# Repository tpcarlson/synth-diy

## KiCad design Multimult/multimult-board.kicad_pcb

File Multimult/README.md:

---
typora-root-url: images
---

# Multimult

##### What is this?

An 8hp, 6 way buffered multiple. For each row, the input is *copied* and the copies are sent to the three output jacks. A small indicator LED per row shows the presence of signal. This buffered multiple is *DC coupled*, which means it's great for both audio and CV use.

##### How much power does it use?

As measured by the joranalogue Test 3, around 50mA on +12v and similar on -12v at peak. The 5v rail is unused.

##### Where does the design come from?

The schematic is based on the Music from outer space DC coupled Voltage Distributor #2, with some tweaks. You can find the original schematics on the MFOS site (http://musicfromouterspace.com/index.php?MAINTAB=SYNTHDIY&VPW=1252&VPH=500).

##### Are there any rare/weird parts used?

No. The design specifies a two-colour LED per input, so you could substitute that for a single colour LED if you only care about positive voltages.

##### Are there any problems with the design?

Not that I'm aware of. Other buffered multiple schematics seem to add a high resistance path to ground for the opamp inputs, but the MFOS design did not - so I skipped it as well. It's worth soldering the two-colour LEDs last after verifying that the positive and negative colours are the right way around - the first LED I soldered red was positive and green negative! A really easy way to check this is to power up the module, feed it some known signals and just touch the legs of your LED to the pads for the LEDs.

##### Do you have a BOM/Mouser cart/Tayda links?

Sorry, no. Things go out of stock so frequently it'd be a lot of work to keep these up to date. Everything in this project is easy to source though, so you should not have any trouble.

##### Can I buy PCBs or a kit?

Send me an email (twigathy+synth@gmail.com)...

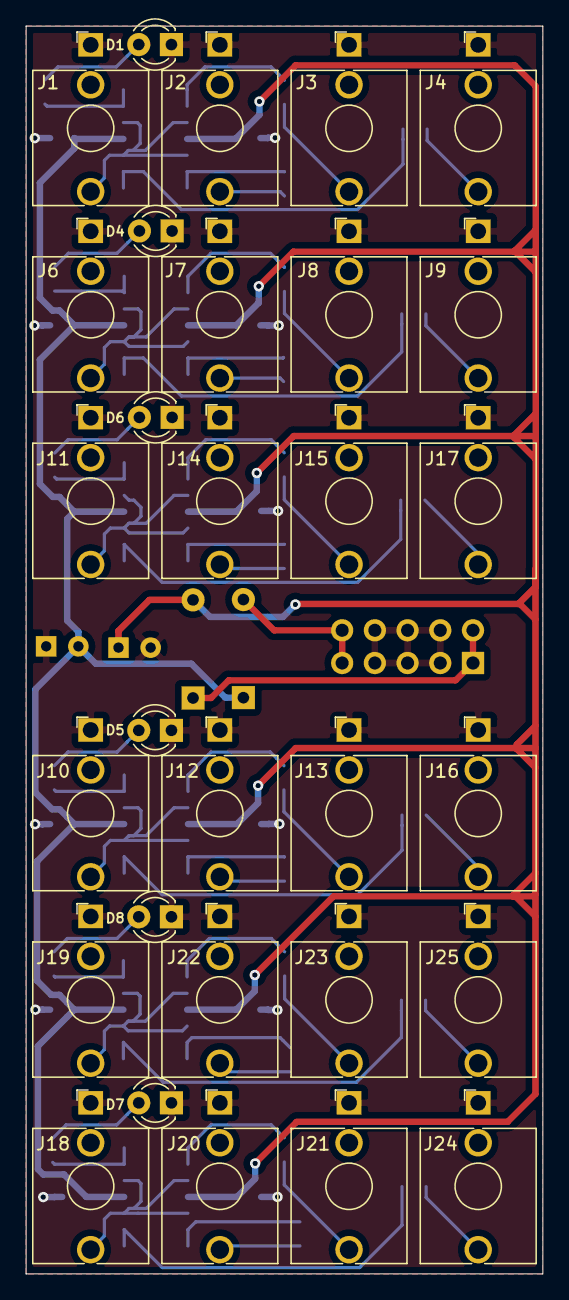
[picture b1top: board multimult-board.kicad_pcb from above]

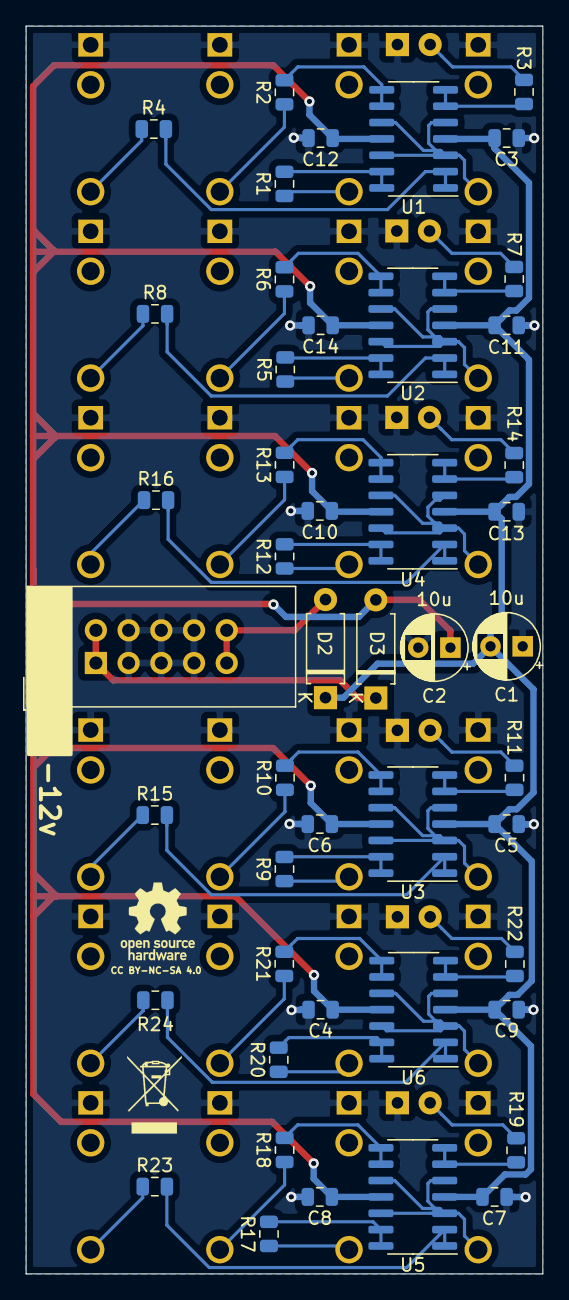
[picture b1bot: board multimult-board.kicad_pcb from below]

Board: 2 copper layers, 40.1 x 96.9 mm, 79 parts (49 on the bottom side), 59 nets.

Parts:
C1, C2: 10u; CP_Radial_D5.0mm_P2.50mm
C3, C4, C5, C6, C7, C8, C9, C10, C11, C12, C13, C14: 100n; C_0805_2012Metric
D1, D4, D5, D6, D7, D8: LED_Dual_2pin; LED_D3.0mm
D2, D3: D_Schottky; D_A-405_P7.62mm_Horizontal
J1, J2, J3, J4, J6, J7, J8, J9, J10, J11, J12, J13, J14, J15, J16, J17, J18, J19, J20, J21, J22, J23, J24, J25: AudioJack2; Jack_3.5mm_QingPu_WQP-PJ398SM_Vertical_CircularHoles
J5: Conn_02x05_Odd_Even; IDC-Header_2x05_P2.54mm_Vertical
J28: WEEE; WEEE-Logo_4.2x6mm_SilkScreen
J29: OSHW; OSHW-Logo_5.7x6mm_SilkScreen
R1, R2, R4, R5, R6, R8, R9, R10, R12, R13, R15, R16, R17, R18, R20, R21, R23, R24: 100R; R_0805_2012Metric
R3, R7, R11, R14, R19, R22: 1k; R_0805_2012Metric
U1, U2, U3, U4, U5, U6: TL074; SOIC-14_3.9x8.7mm_P1.27mm

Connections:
+12V: C1.2, C3.1, C5.1, C7.1, C9.1, C11.1, C13.1, D2.1, U1.4, U2.4, U3.4, U4.4, U5.4, U6.4
-12V: C2.1, C4.1, C6.1, C8.1, C10.1, C12.1, C14.1, D3.2, U1.11, U2.11, U3.11, U4.11, U5.11, U6.11
Earth: C1.1, C2.2, C3.2, C4.2, C5.2, C6.2, C7.2, C8.2, C9.2, C10.2, C11.2, C12.2, C13.2, C14.2, D1.1, D4.1, D5.1, D6.1, D7.1, D8.1, J1.S, J2.S, J3.S, J4.S, J5.3, J5.4, J5.5, J5.6, J5.7, J5.8, J6.S, J7.S, J8.S, J9.S, J10.S, J11.S, J12.S, J13.S, J14.S, J15.S, J16.S, J17.S, J18.S, J19.S, J20.S, J21.S, J22.S, J23.S, J24.S, J25.S
unnamed: D1.2, R3.1
unnamed: D2.2, J5.9, J5.10
unnamed: D3.1, J5.1, J5.2
unnamed: D4.2, R7.1
unnamed: D5.2, R11.1
unnamed: D6.2, R14.1
unnamed: D7.2, R19.1
unnamed: D8.2, R22.1
unnamed: J1.T, U1.3, U1.5, U1.10, U1.12
unnamed: J2.T, R1.1
unnamed: J3.T, R2.1
unnamed: J4.T, R4.1
unnamed: J6.T, U2.3, U2.5, U2.10, U2.12
unnamed: J7.T, R5.1
unnamed: J8.T, R6.1
unnamed: J9.T, R8.1
unnamed: J10.T, U3.3, U3.5, U3.10, U3.12
unnamed: J11.T, U4.3, U4.5, U4.10, U4.12
unnamed: J12.T, R9.1
unnamed: J13.T, R10.1
unnamed: J14.T, R12.1
unnamed: J15.T, R13.1
unnamed: J16.T, R15.1
unnamed: J17.T, R16.1
unnamed: J18.T, U5.3, U5.5, U5.10, U5.12
unnamed: J19.T, U6.3, U6.5, U6.10, U6.12
unnamed: J20.T, R17.1
unnamed: J21.T, R18.1
unnamed: J22.T, R20.1
unnamed: J23.T, R21.1
unnamed: J24.T, R23.1
unnamed: J25.T, R24.1
unnamed: R1.2, U1.13, U1.14
unnamed: R2.2, U1.8, U1.9
unnamed: R3.2, U1.6, U1.7
unnamed: R4.2, U1.1, U1.2
unnamed: R5.2, U2.13, U2.14
unnamed: R6.2, U2.8, U2.9
unnamed: R7.2, U2.6, U2.7
unnamed: R8.2, U2.1, U2.2
unnamed: R9.2, U3.13, U3.14
unnamed: R10.2, U3.8, U3.9
unnamed: R11.2, U3.6, U3.7
unnamed: R12.2, U4.13, U4.14
unnamed: R13.2, U4.8, U4.9
unnamed: R14.2, U4.6, U4.7
unnamed: R15.2, U3.1, U3.2
unnamed: R16.2, U4.1, U4.2
unnamed: R17.2, U5.13, U5.14
unnamed: R18.2, U5.8, U5.9
unnamed: R19.2, U5.6, U5.7
unnamed: R20.2, U6.13, U6.14
unnamed: R21.2, U6.8, U6.9
unnamed: R22.2, U6.6, U6.7
unnamed: R23.2, U5.1, U5.2
unnamed: R24.2, U6.1, U6.2

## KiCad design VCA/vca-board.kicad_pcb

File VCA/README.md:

# VCA

##### What is this?

A straightforward 2-channel VCA with CV inputs and an offset per channel. Basically, makes noise quieter (or anything else you want to modulate).

##### How much power does it use?

Next to nothing! Around 10ma on both +/- 12v when both channels are fully "open".

##### Where does the design come from?

This is almost a complete copy of the schematic from [this wonderful ElectricDruid article.](https://electricdruid.net/design-a-eurorack-vintage-vca-with-the-lm13700/)

##### Are there any rare/weird parts used?

The LM13700 is about the most exotic thing in the design, and that can be found pretty much everywhere - I got mine from RS in the UK.

##### Are there any problems with the design?

While the component layout is pretty neat and tidy, the routing is an absolute disaster. In spite of that it all still works and doesn't sound noisy or anything like that.

The resistor footprints on the PCB are also a little small, so I had to stand my resistors up. If you used 1/8th watt resistors they'd probably fit fine.

Finally, I also somehow neglected to add power decoupling for the +/-12v rails at the power connector, but there is reverse polarity protection present.

If I were to give this a second try, I'd add state LEDs to everything (CV, input, output) and probably make the panel just a touch wider to allow for better ergonomics. You might get by with skinny trimmer potentiometers but I'm personally not much of a fan of those.

##### Do you have a BOM/Mouser cart/Tayda links?

Sorry, no. Things go out of stock so frequently it'd be a lot of work to keep these up to date. Everything in this project is easy to source though, so you should not have any trouble.

##### Can I buy PCBs or a kit?

Send me an email (twigathy+synth@gmail.com)...

(Add some rendered images of the panel and back of PCB(s).)

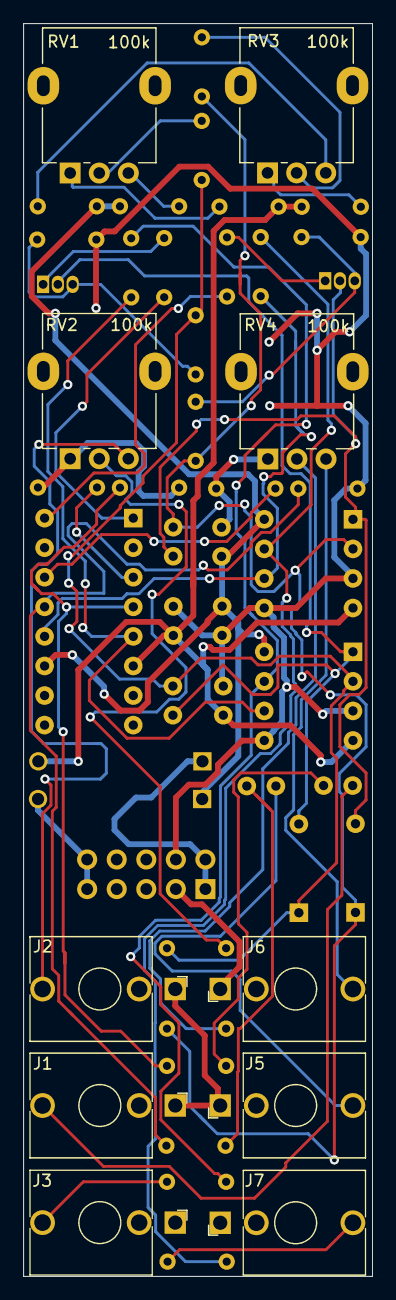
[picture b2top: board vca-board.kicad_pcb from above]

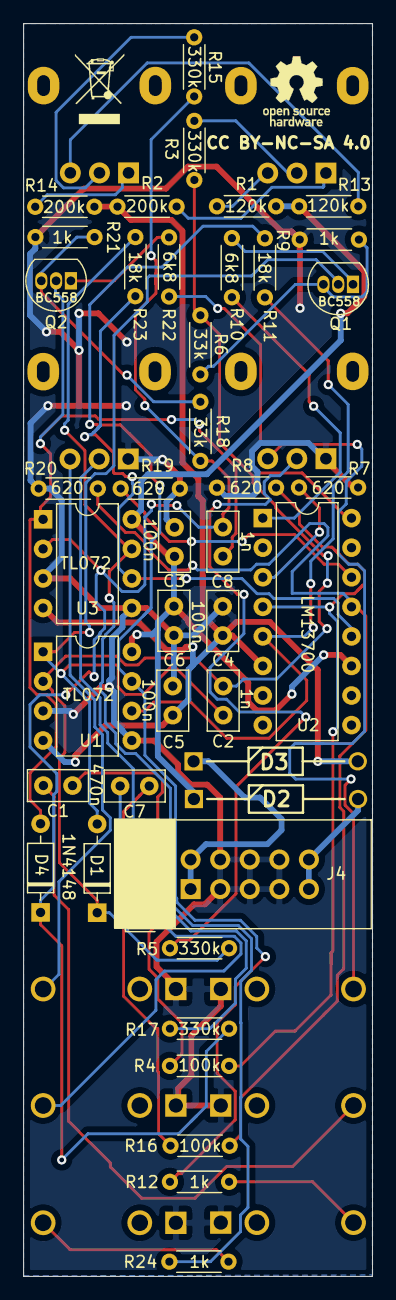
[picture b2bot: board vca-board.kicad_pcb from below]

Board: 2 copper layers, 30.0 x 107.6 mm, 54 parts (44 on the bottom side), 39 nets.

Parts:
C1, C7: 470n; C_Disc_D5.0mm_W2.5mm_P2.50mm
C2, C8: 1n; C_Disc_D5.0mm_W2.5mm_P2.50mm
C3, C4, C5, C6: 100n; C_Disc_D5.0mm_W2.5mm_P2.50mm
D1, D4: 1N4148; D_DO-35_SOD27_P7.62mm_Horizontal
D2, D3: D_Schottky; DIOAD1405W86L465D235
J1, J2, J3, J5, J6, J7: AudioJack2; Jack_3.5mm_QingPu_WQP-PJ398SM_Vertical_CircularHoles
J4: Conn_02x05_Odd_Even; IDC-Header_2x05_P2.54mm_Vertical
J26: WEEE; WEEE-Logo_4.2x6mm_SilkScreen
J27: OSHW; OSHW-Logo_5.7x6mm_SilkScreen
Q1, Q2: BC558; TO-92_Inline
R1, R13: 120k; R_Axial_DIN0204_L3.6mm_D1.6mm_P5.08mm_Horizontal
R2, R14: 200k; R_Axial_DIN0204_L3.6mm_D1.6mm_P5.08mm_Horizontal
R3, R5, R15, R17: 330k; R_Axial_DIN0204_L3.6mm_D1.6mm_P5.08mm_Horizontal
R4, R16: 100k; R_Axial_DIN0204_L3.6mm_D1.6mm_P5.08mm_Horizontal
R6, R18: 33k; R_Axial_DIN0204_L3.6mm_D1.6mm_P5.08mm_Horizontal
R7, R8, R19, R20: 620; R_Axial_DIN0204_L3.6mm_D1.6mm_P5.08mm_Horizontal
R9, R12, R21, R24: 1k; R_Axial_DIN0204_L3.6mm_D1.6mm_P5.08mm_Horizontal
R10, R22: 6k8; R_Axial_DIN0204_L3.6mm_D1.6mm_P5.08mm_Horizontal
R11, R23: 18k; R_Axial_DIN0204_L3.6mm_D1.6mm_P5.08mm_Horizontal
RV1, RV2, RV3, RV4: 100k; Potentiometer_Alpha_RD901F-40-00D_Single_Vertical
U1, U3: TL072; DIP-8_W7.62mm
U2: LM13700; DIP-16_W7.62mm

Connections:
+12V: C3.1, C6.2, D2.1, R1.2, R13.2, U1.8, U2.11, U3.8
-12V: C4.1, C5.1, D3.2, R2.2, R14.2, U1.4, U2.6, U3.4
Earth: C3.2, C4.2, C5.2, C6.1, J1.S, J2.S, J3.S, J4.3, J4.4, J4.5, J4.6, J4.7, J4.8, J5.S, J6.S, J7.S, R7.2, R8.2, R9.1, R19.2, R20.2, R21.1, RV2.1, RV4.1, U1.3, U1.5, U3.3, U3.5
unnamed: C1.1, R4.2
unnamed: C1.2, J1.T
unnamed: C2.1, D1.2, Q1.2, U1.1
unnamed: C2.2, D1.1, R3.1, R5.1, R6.2, U1.2
unnamed: C7.1, R16.2
unnamed: C7.2, J5.T
unnamed: C8.1, D4.2, Q2.2, U3.1
unnamed: C8.2, D4.1, R15.1, R17.1, R18.2, U3.2
unnamed: D2.2, J4.9, J4.10
unnamed: D3.1, J4.1, J4.2
unnamed: J2.T, RV2.3
unnamed: J3.T, R12.1
unnamed: J6.T, RV4.3
unnamed: J7.T, R24.1
unnamed: Q1.1, R10.1
unnamed: Q1.3, R6.1, R9.2
unnamed: Q2.1, R22.1
unnamed: Q2.3, R18.1, R21.2
unnamed: R1.1, RV1.3
unnamed: R2.1, RV1.1
unnamed: R3.2, RV1.2
unnamed: R4.1, R8.1, U2.4
unnamed: R5.2, RV2.2
unnamed: R7.1, U2.3
unnamed: R10.2, U2.1
unnamed: R11.1, R12.2, U1.7
unnamed: R11.2, U1.6, U2.5
unnamed: R13.1, RV3.3
unnamed: R14.1, RV3.1
unnamed: R15.2, RV3.2
unnamed: R16.1, R20.1, U2.13
unnamed: R17.2, RV4.2
unnamed: R19.1, U2.14
unnamed: R22.2, U2.16
unnamed: R23.1, R24.2, U3.7
unnamed: R23.2, U2.12, U3.6

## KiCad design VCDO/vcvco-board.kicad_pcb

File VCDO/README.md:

# VCDO

##### What is this?

A 10hp Wavetable oscillator with 1v/octave control, pitch, bitcrush, glide, and a separate sub-oscillator output.

##### How much power does it use?

As measured by the Joranalogue Test 3, around 40 mA on +12v and 10 mA on -12v at peak. The 5v rail is unused.

##### Where does the design come from?

The original schematic is from the datasheet for the VCDO chip on the ElectricDruid website (https://electricdruid.net/product/vcdo-wavetable-oscillator/). There were a couple of tweaks to add test points and buffered LED drivers for the main and sub-oscillator outputs.

##### Are there any rare/weird parts used?

If you're handy at flashing PIC chips you can flash  your own, however I'd strongly suggest supporting ElectricDruid and buying chips from them directly instead! Other than that, there are no exotic parts used. Some of the resistor values are _little_ less common, but resistors are very cheap. I just got 50-packs of values I didn't have for less than £1 each.

##### Are there any problems with the design?

Quite a few, but nothing that has proven to be a killer so far... Here are some things I'd like to improve if ever there were a v2

- Some of the controls are "reversed", such as the bitcrush, frequency and fine controls. I think this comes from me misreading the original schematic a little. I have not fixed the Kicad schematics here yet!
- The space between the Glide control and Glide toggle is a bit limited. It would have probably been better to mount the Glide toggle just a little further down, between the control and the input jacks
- While I specified a dual-colour LED it turns out that's not really very interesting at VCO rates. You could easily swap that out for a single-colour LED provided you get the polarity right
- The LEDs at the top are a little close to the controls, I made sure only a little of the dome of my LEDs was poking out. If you are building one yourself, you can do this, use a flat-topped LED, or even use light pipes and an SMD LED on the LED pads...
- It would've been nice to include LED indicators for CV parameters, but there was not enough board space, and I'm not really sure where on the panel they could usefully go either
- The vertically mounted resistors work fine, but now that I know SMD assembly isn't really that expensive, maybe go for surface mount and have them pre-soldered next time around
- Calibration trimmers worked fine, but the test points a little fiddly to access - keep them further away from other parts in future

##### Do you have a BOM/Mouser cart/Tayda links?

Sorry, no. Things go out of stock so frequently it'd be a lot of work to keep these up to date. Everything in this project is easy to source though, so you should not have any trouble.

##### Can I buy PCBs or a kit?

Send me an email (twigathy+synth@gmail.com)...

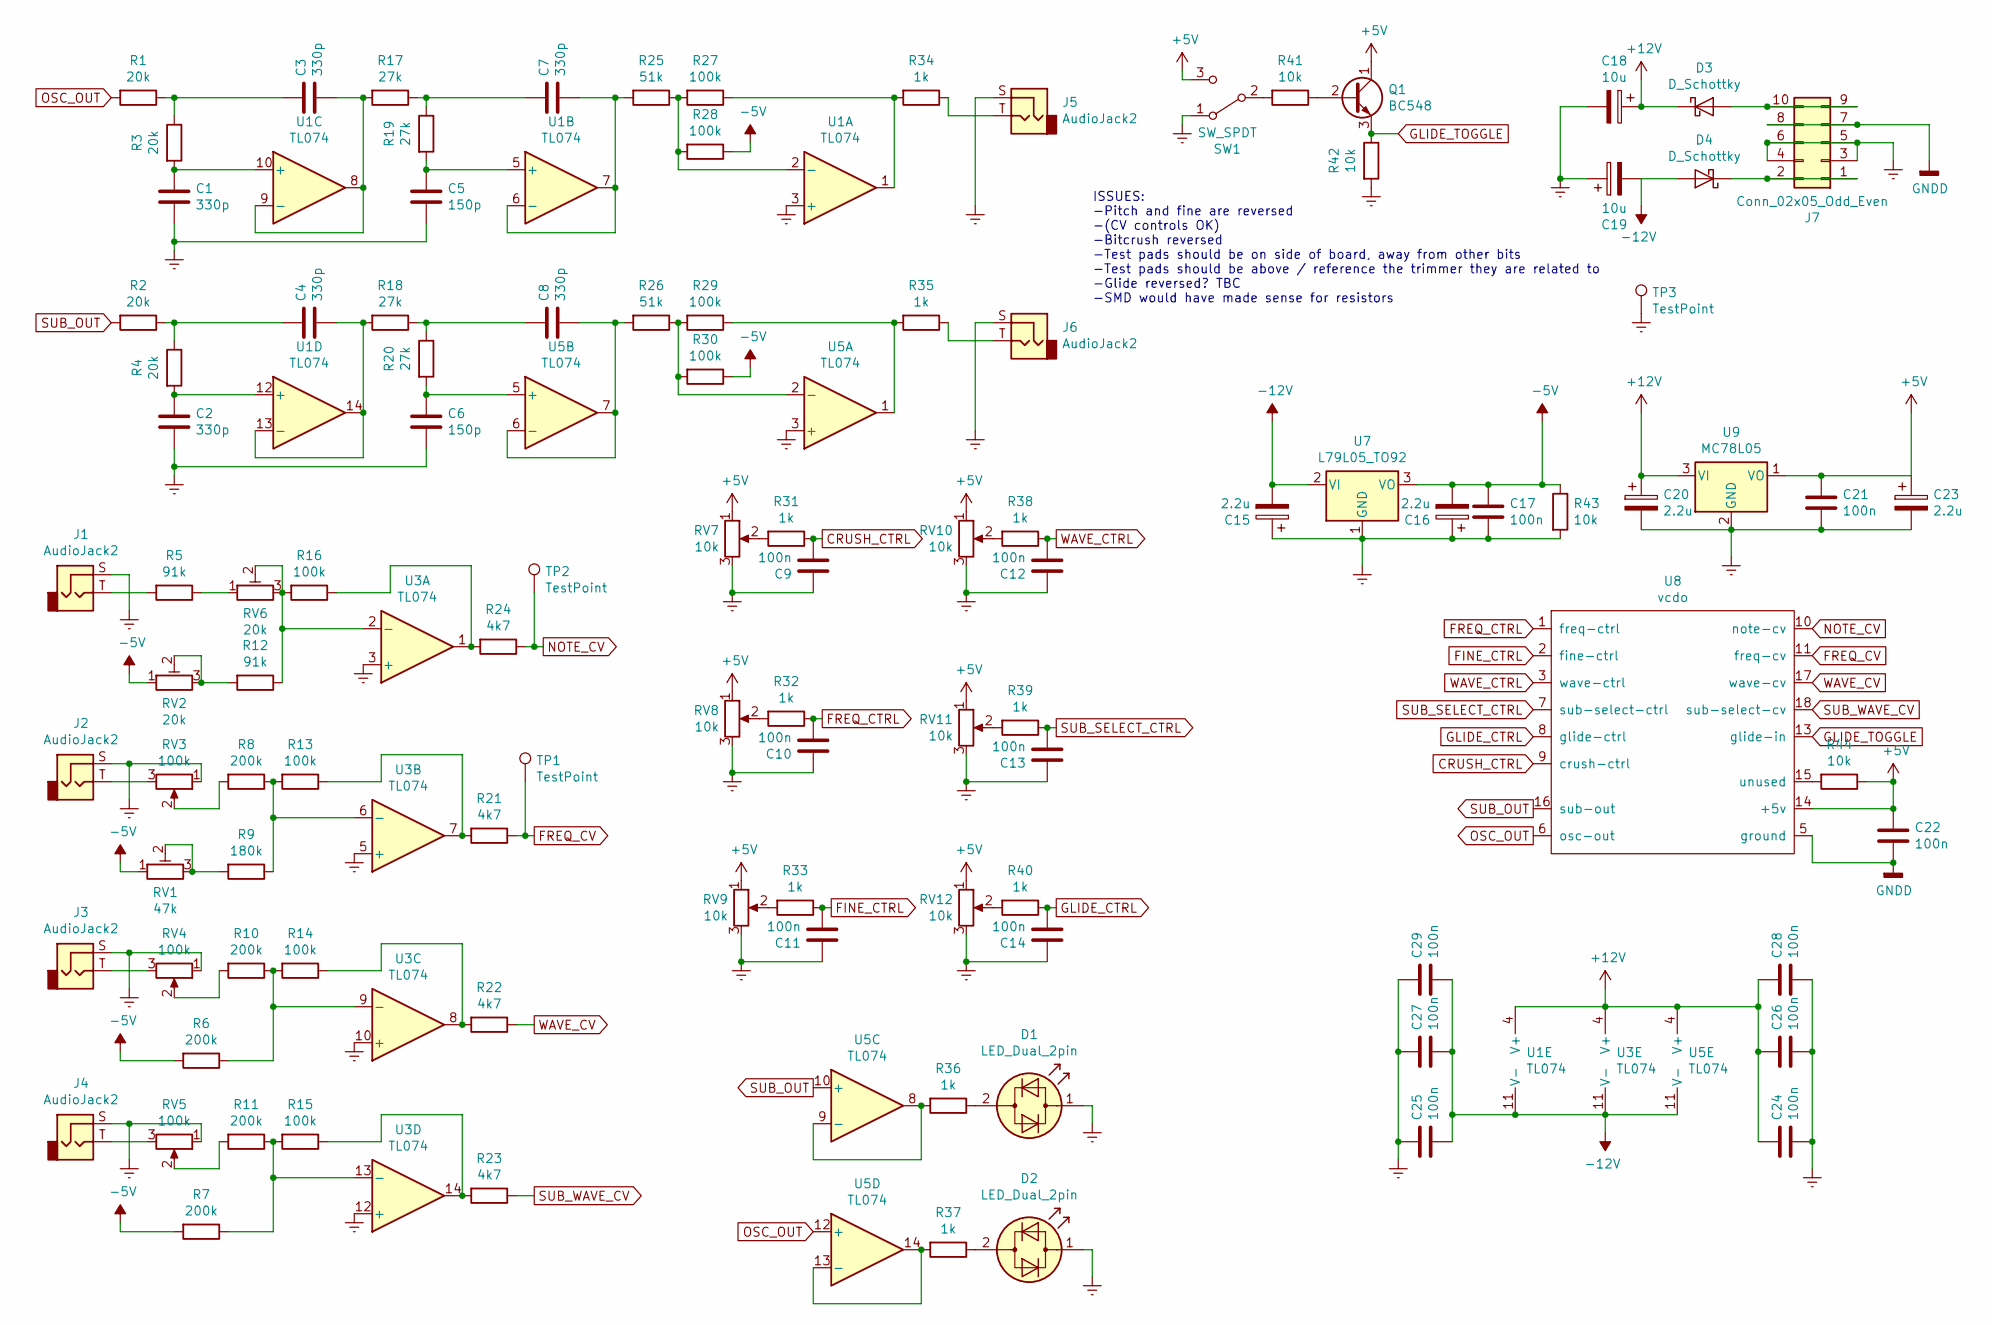
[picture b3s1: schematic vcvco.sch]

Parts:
C1, C2, C3, C4, C7, C8: 330p; C_Disc_D5.0mm_W2.5mm_P2.50mm
C5, C6: 150p; C_Disc_D5.0mm_W2.5mm_P2.50mm
C9, C10, C11, C12, C13, C14, C17, C21, C22, C24, C25, C26, C27, C28, C29: 100n; C_Disc_D5.0mm_W2.5mm_P2.50mm
C15, C16, C20, C23: 2.2u; CP_Radial_D5.0mm_P2.50mm
C18, C19: 10u; CP_Radial_D5.0mm_P2.50mm
D1, D2: LED_Dual_2pin; LED_D5.0mm
D3, D4: D_Schottky; D_A-405_P7.62mm_Horizontal
J1, J2, J3, J4, J5, J6: AudioJack2; Jack_3.5mm_QingPu_WQP-PJ398SM_Vertical_CircularHoles
J7: Conn_02x05_Odd_Even; IDC-Header_2x05_P2.54mm_Vertical
Q1: BC548; TO-92_Inline
R1, R2, R3, R4: 20k; R_Axial_DIN0207_L6.3mm_D2.5mm_P2.54mm_Vertical
R5, R12: 91k; R_Axial_DIN0207_L6.3mm_D2.5mm_P2.54mm_Vertical
R6, R7, R8, R10, R11: 200k; R_Axial_DIN0207_L6.3mm_D2.5mm_P2.54mm_Vertical
R9: 180k; R_Axial_DIN0207_L6.3mm_D2.5mm_P2.54mm_Vertical
R13, R14, R15, R16, R27, R28, R29, R30: 100k; R_Axial_DIN0207_L6.3mm_D2.5mm_P2.54mm_Vertical
R17, R18, R19, R20: 27k; R_Axial_DIN0207_L6.3mm_D2.5mm_P2.54mm_Vertical
R21, R22, R23, R24: 4k7; R_Axial_DIN0207_L6.3mm_D2.5mm_P2.54mm_Vertical
R25, R26: 51k; R_Axial_DIN0207_L6.3mm_D2.5mm_P2.54mm_Vertical
R31, R32, R33, R34, R35, R36, R37, R38, R39, R40: 1k; R_Axial_DIN0207_L6.3mm_D2.5mm_P2.54mm_Vertical
R41, R42, R43: 10k; R_Axial_DIN0207_L6.3mm_D2.5mm_P2.54mm_Vertical
R44: 10k; R_Axial_DIN0207_L6.3mm_D2.5mm_P7.62mm_Horizontal
RV1: 47k; sub-mini-spdt-thonk
RV2, RV6: 20k; sub-mini-spdt-thonk
RV3, RV4, RV5: 100k; Potentiometer_Alpha_RD901F-40-00D_Single_Vertical
RV7, RV8, RV9, RV10, RV11, RV12: 10k; Potentiometer_Alpha_RD901F-40-00D_Single_Vertical
SW1: SW_SPDT; sub-mini-spdt-thonk
TP1, TP2, TP3: TestPoint; TestPoint_THTPad_D2.5mm_Drill1.2mm
U1, U3, U5: TL074; DIP-14_W7.62mm
U7: L79L05_TO92; TO-92_Inline
U8: vcdo; DIP-18_W7.62mm
U9: MC78L05; TO-92_Inline

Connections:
+5V: C21.1, C22.1, C23.1, Q1.1 (C), R44.1, RV7.1, RV8.1, RV9.1, RV10.1, RV11.1, RV12.1, SW1.3 (C), U8.14 (+5v), U9.1 (VO)
+12V: C18.1, C20.1, C24.1, C26.1, C28.1, D3.1 (K), U1.4 (V+), U3.4 (V+), U5.4 (V+), U9.3 (VI)
-5V: C16.2, C17.1, R6.2, R7.2, R28.1, R30.1, R43.1, RV1.1, RV2.1, U7.3 (VO)
-12V: C15.2, C19.2, C25.2, C27.2, C29.2, D4.2 (A), U1.11 (V-), U3.11 (V-), U5.11 (V-), U7.2 (VI)
CRUSH_CTRL: C9.2, R31.1, U8.9 (crush-ctrl)
Earth: C1.2, C2.2, C5.2, C6.2, C9.1, C10.1, C11.1, C12.1, C13.1, C14.1, C15.1, C16.1, C17.2, C18.2, C19.1, C20.2, C21.2, C23.2, C24.2, C25.1, C26.2, C27.1, C28.2, C29.1, D1.1 (KA), D2.1 (KA), J1.S, J2.S, J3.S, J4.S, J5.S, J6.S, J7.3, J7.4, J7.5, J7.6, R42.2, R43.2, RV3.1, RV4.1, RV5.1, RV7.3, RV8.3, RV9.3, RV10.3, RV11.3, RV12.3, SW1.1 (A), TP3.1, U1.3 (+), U3.3 (+), U3.5 (+), U3.10 (+), U3.12 (+), U5.3 (+), U7.1 (GND), U9.2 (GND)
FINE_CTRL: C11.2, R33.1, U8.2 (fine-ctrl)
FREQ_CTRL: C10.2, R32.1, U8.1 (freq-ctrl)
FREQ_CV: R21.1, TP1.1, U8.11 (freq-cv)
GLIDE_CTRL: C14.2, R40.1, U8.8 (glide-ctrl)
GLIDE_TOGGLE: Q1.3 (E), R42.1, U8.13 (glide-in)
GNDD: C22.2, J7.7, J7.8, U8.5 (ground)
NOTE_CV: R24.1, TP2.1, U8.10 (note-cv)
unnamed: C1.1, R3.2, U1.10 (+)
unnamed: C2.1, R4.2, U1.12 (+)
unnamed: C3.1, R1.1, R3.1
unnamed: C3.2, R17.2, U1.8, U1.9 (-)
unnamed: C4.1, R2.1, R4.1
unnamed: C4.2, R18.2, U1.13 (-), U1.14
unnamed: C5.1, R19.2, U1.5 (+)
unnamed: C6.1, R20.2, U5.5 (+)
unnamed: C7.1, R17.1, R19.1
unnamed: C7.2, R25.2, U1.6 (-), U1.7
unnamed: C8.1, R18.1, R20.1
unnamed: C8.2, R26.2, U5.6 (-), U5.7
unnamed: D1.2 (AK), R36.1
unnamed: D2.2 (AK), R37.1
unnamed: D3.2 (A), J7.9, J7.10
unnamed: D4.1 (K), J7.1, J7.2
unnamed: J1.T, R5.2
unnamed: J2.T, RV3.3
unnamed: J3.T, RV4.3
unnamed: J4.T, RV5.3
unnamed: J5.T, R34.1
unnamed: J6.T, R35.1
unnamed: Q1.2 (B), R41.1
unnamed: R5.1, RV6.1
unnamed: R8.2, RV3.2
unnamed: R9.2, RV1.2, RV1.3
unnamed: R6.1, R10.1, R14.2, U3.9 (-)
unnamed: R10.2, RV4.2
unnamed: R7.1, R11.1, R15.2, U3.13 (-)
unnamed: R11.2, RV5.2
unnamed: R12.1, R16.2, RV6.2, RV6.3, U3.2 (-)
unnamed: R12.2, RV2.2, RV2.3
unnamed: R13.1, R21.2, U3.7
unnamed: R8.1, R9.1, R13.2, U3.6 (-)
unnamed: R14.1, R22.2, U3.8
unnamed: R15.1, R23.2, U3.14
unnamed: R16.1, R24.2, U3.1
unnamed: R25.1, R27.2, R28.2, U1.2 (-)
unnamed: R26.1, R29.2, R30.2, U5.2 (-)
unnamed: R27.1, R34.2, U1.1
unnamed: R29.1, R35.2, U5.1
unnamed: R31.2, RV7.2
unnamed: R32.2, RV8.2
unnamed: R33.2, RV9.2
unnamed: R36.2, U5.8, U5.9 (-)
unnamed: R37.2, U5.13 (-), U5.14
unnamed: R38.2, RV10.2
unnamed: R39.2, RV11.2
unnamed: R40.2, RV12.2
unnamed: R41.2, SW1.2 (B)
unnamed: R44.2, U8.15 (unused)
OSC_OUT: R1.2, U5.12 (+), U8.6 (osc-out)
SUB_OUT: R2.2, U5.10 (+), U8.16 (sub-out)
SUB_SELECT_CTRL: C13.2, R39.1, U8.7 (sub-select-ctrl)
SUB_WAVE_CV: R23.1, U8.18 (sub-select-cv)
WAVE_CTRL: C12.2, R38.1, U8.3 (wave-ctrl)
WAVE_CV: R22.1, U8.17 (wave-cv)

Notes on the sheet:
ISSUES: -Pitch and fine are reversed -(CV controls OK) -Bitcrush reversed -Test pads should be on side of board, away from other bits -Test pads should be above / reference the trimmer they are related to -Glide reversed? TBC -SMD would have made sense for resistors

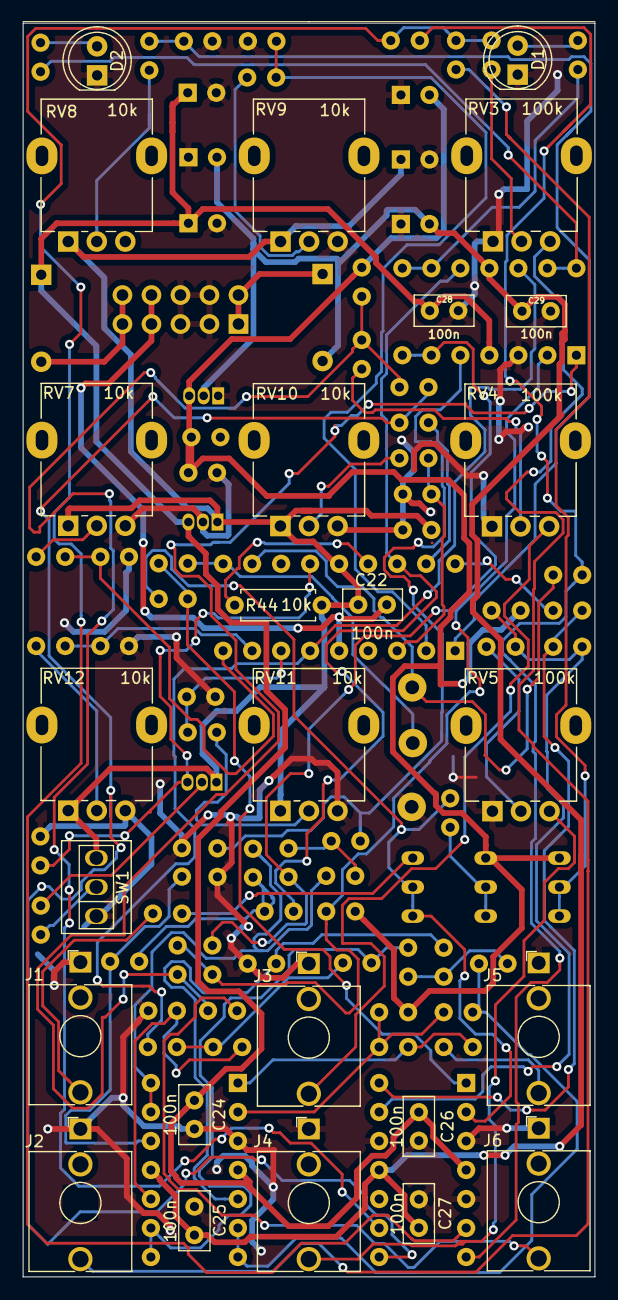
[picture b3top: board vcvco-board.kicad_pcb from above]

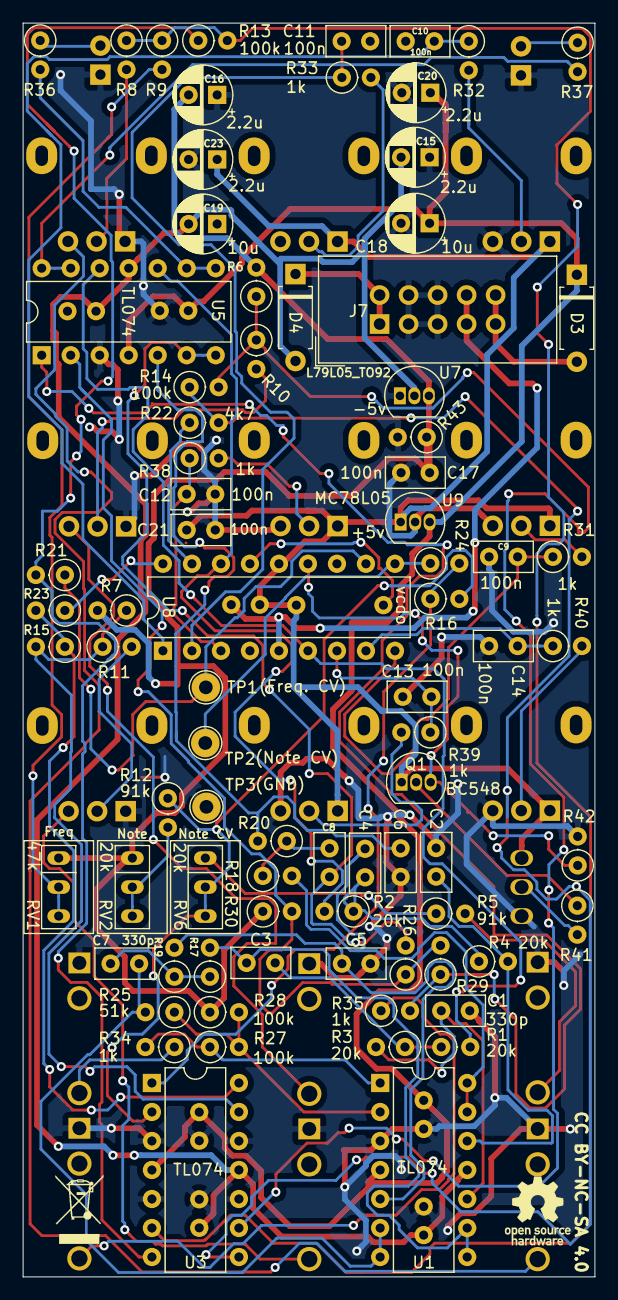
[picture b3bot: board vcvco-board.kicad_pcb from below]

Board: 2 copper layers, 50.1 x 109.8 mm, 109 parts (83 on the bottom side), 70 nets.

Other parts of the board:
J26: WEEE; WEEE-Logo_4.2x6mm_SilkScreen
J27: OSHW; OSHW-Logo_5.7x6mm_SilkScreen

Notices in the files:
Multimult/multimult-board.kicad_pcb:
CC BY-NC-SA 4.0
